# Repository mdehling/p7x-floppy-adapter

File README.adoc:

= IBM PS/2 P7X Floppy Drive Adapter
Malte Dehling <mdehling@gmail.com>

:imagesdir: https://raw.githubusercontent.com/mdehling/p7x-floppy-adapter/main/img/

:url-Ohland-P70: https://ardent-tool.com/8573/P70.html
:url-TubeTimeUS-Twitter: https://twitter.com/tubetimeus
:url-TubeTimeUS-PS2FloppyAdapter: https://github.com/schlae/PS2FloppyAdapter
:url-Aisler: https://aisler.net/
:url-KiCad: https://kicad.org/

A well-known weakness of the portable IBM PS/2 models P70 and P75 is their
floppy drive.  Many of the drives have failed due to leaking capacitors and/or
problems stemming from their vertical orientation.  This adapter is designed
to allow replacing a failed IBM drive with a standard PC floppy drive.

For a similar project for the less portable IBM PS/2 Model 50(Z) and Model 70,
check out {url-TubeTimeUS-Twitter}[@TubeTimeUS]'s
{url-TubeTimeUS-PS2FloppyAdapter}[PS/2 floppy drive adapter].  It was after I
found his project that I had the idea to make this version for the P7X.

Parts
-----
I designed the PCB using {url-KiCad}[KiCad 5] and ordered a small batch from
{url-Aisler}[Aisler], of which there are still some left.  Feel free to send
me an email!

Apart from the PCB, you will need the following components:

[%autowidth]
|===
| Designator | Quantity | Description

| J1         | 1        | 2x17 2.54mm shrouded pin header
| J2         | 1        | 2x17 2.54mm socket header
| J3         | 1        | floppy power connector
| R1–R6      | 6        | 1k 0.25W 5% axial resistor
|===

Assembly
--------
Assembling the adapter is pretty straightforward, see the photos below.  Note
that in trying to keep the PCB small enough to physically fit in the P7X, I
had to place the components very close together.  If you use a shrouded pin
header for J1, it is easy to accidentally cover some of the neighboring
through-holes.  In my experience, the easiest way to avoid this is to solder
on the P7X-side header J1 last.

Most newer floppy drives do not need the +12V line, e.g., both of the drives I
tested work with just +5V connected.  It is there, however, in case some other
drive needs it.

link:{imagesdir}front.jpg[image:front.jpg["Front Side",width=32%]]
link:{imagesdir}back.jpg[image:back.jpg["Back Side",width=32%]]
link:{imagesdir}mounted.jpg[image:mounted.jpg["Mounted Adapter",width=32%]]

Installing the Drive
--------------------
Read link:{url-Ohland-P70}[Louis Ohland's P70 page] for information on how to
remove (and install) the floppy drive.  It contains a lot of other useful
information on the P70, too.

I have personally tested the adapter with the following drive models:

* NEC FD1231H
* TEAC FD-235HF

If you end up using this adapter (or fail to) with other drives, please let me
know so I can include that information on this page.

With both drive models, I had to remove the plastic front bezel for the drive
to fit.  The eject button for the NEC FD1231H fits the hole in the P7X's drive
cover.  It is not centered and a little too small, but it works well enough.
In the case of the TEAC FD-235HF, you will have to file the eject button down
a little to make it fit.  @TubeTimeUS's project above also contains an STL
file for a custom eject button for the TEAC FD-235HF.  I have not yet tried
whether it fits the P7X.

Permanently Converting a Drive
------------------------------
Another option I explored is permanently converting a disk drive by soldering
on a converter board.  One advantage of this approach is, that the resulting
converted drive is smaller than a drive with an adapter plugged in.  This
makes it a little easier to install.  The downside is, of course, that there
is no easy way to go back.

This is what a converted TEAC FD-235HF drive looks like:

link:{imagesdir}teac-fd-235hf_1.jpg[image:teac-fd-235hf_1.jpg["At an Angle",width=32%]]
link:{imagesdir}teac-fd-235hf_2.jpg[image:teac-fd-235hf_2.jpg["Back Side",width=32%]]
link:{imagesdir}teac-fd-235hf_3.jpg[image:teac-fd-235hf_3.jpg["From Above",width=32%]]

And here is how it compares to the ALPS-produced IBM floppy drive:

link:{imagesdir}ibm_vs_teac-fd-235hf_1.jpg[image:ibm_vs_teac-fd-235hf_1.jpg["From the Side",width=32%]]
link:{imagesdir}ibm_vs_teac-fd-235hf_2.jpg[image:ibm_vs_teac-fd-235hf_2.jpg["From Behind",width=32%]]

You can find the KiCad PCB in the `+converter/+` directory should you want to
follow this path.

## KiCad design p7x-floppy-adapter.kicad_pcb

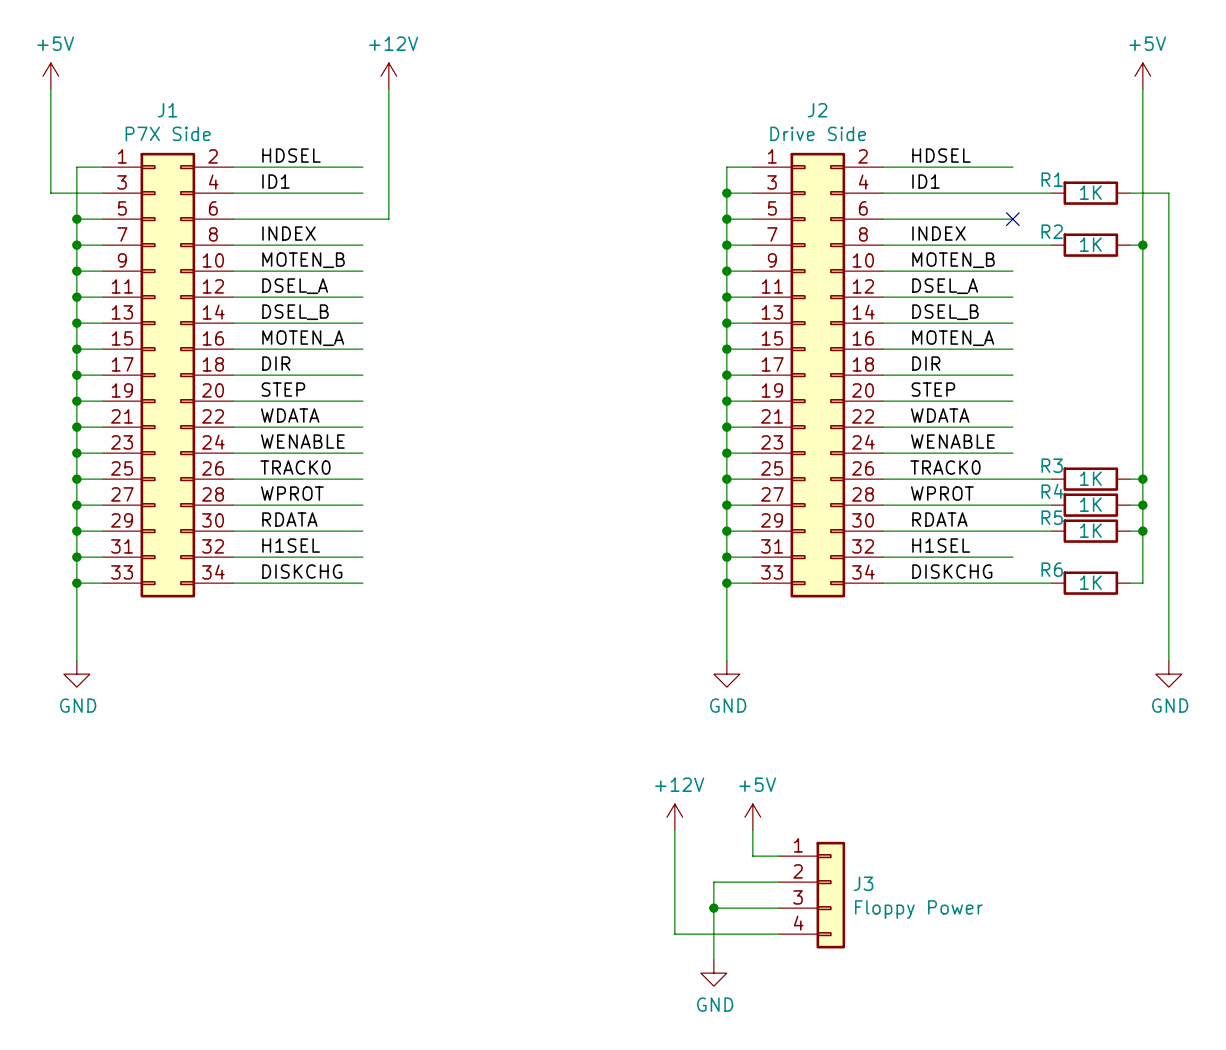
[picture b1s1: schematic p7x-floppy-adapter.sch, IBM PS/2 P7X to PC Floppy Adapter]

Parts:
J1: P7X Side; PinHeader_2x17_P2.54mm_Vertical
J2: Drive Side; PinSocket_2x17_P2.54mm_Vertical
J3: Floppy Power; SolderWire-0.15sqmm_1x04_P2.54mm_D0.5mm_OD1.5mm_Relief
R1, R2, R3, R4, R5, R6: 1K; R_Axial_DIN0207_L6.3mm_D2.5mm_P2.54mm_Vertical

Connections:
+5V: J1.3, J3.1, R2.1, R3.1, R4.1, R5.1, R6.1
+12V: J1.6, J3.4
/DIR: J1.18, J2.18
/DISKCHG: J1.34, J2.34, R6.2
/DSEL_A: J1.12, J2.12
/DSEL_B: J1.14, J2.14
/H1SEL: J1.32, J2.32
/HDSEL: J1.2, J2.2
/ID1: J1.4, J2.4, R1.2
/INDEX: J1.8, J2.8, R2.2
/MOTEN_A: J1.16, J2.16
/MOTEN_B: J1.10, J2.10
/RDATA: J1.30, J2.30, R5.2
/STEP: J1.20, J2.20
/TRACK0: J1.26, J2.26, R3.2
/WDATA: J1.22, J2.22
/WENABLE: J1.24, J2.24
/WPROT: J1.28, J2.28, R4.2
GND: J1.1, J1.5, J1.7, J1.9, J1.11, J1.13, J1.15, J1.17, J1.19, J1.21, J1.23, J1.25, J1.27, J1.29, J1.31, J1.33, J2.1, J2.3, J2.5, J2.7, J2.9, J2.11, J2.13, J2.15, J2.17, J2.19, J2.21, J2.23, J2.25, J2.27, J2.29, J2.31, J2.33, J3.2, J3.3, R1.1

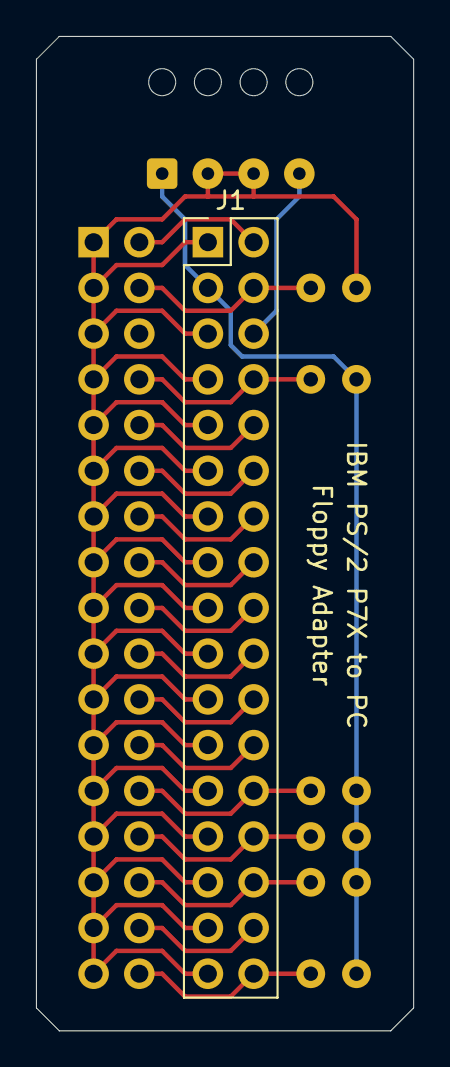
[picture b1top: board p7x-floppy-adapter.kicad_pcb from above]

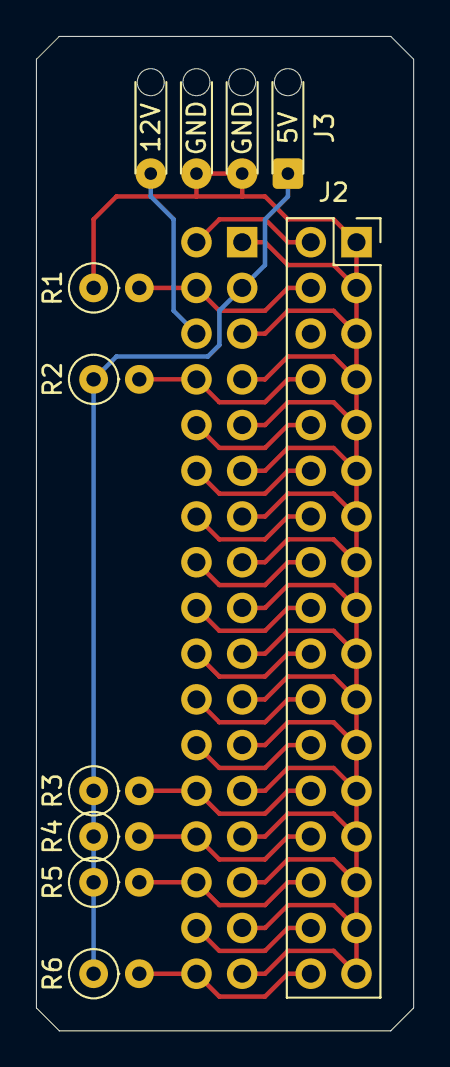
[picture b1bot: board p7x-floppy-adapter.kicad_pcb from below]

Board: 2 copper layers, 21.0 x 55.2 mm, 9 parts (8 on the bottom side), 19 nets.

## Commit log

2021-04-23 Add converter for TEAC FD-235HF
2021-04-23 Adjust for TEAC FD-235HF-6291
2022-01-25 Update Ohland's P70 page link
2022-05-27 Update image URLs
